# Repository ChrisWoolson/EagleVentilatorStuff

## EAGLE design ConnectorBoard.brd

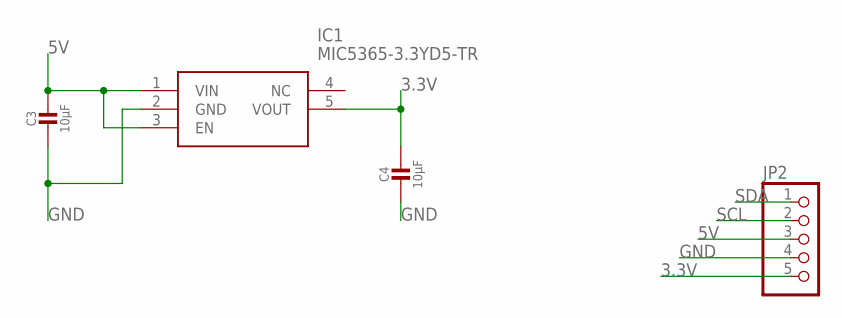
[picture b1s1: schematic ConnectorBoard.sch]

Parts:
C3, C4: 10µF; 0805-NO
IC1: MIC5365-3.3YD5-TR; SOT95P280X100-5N
JP2: PINHD-1X55X2MM; 1_05X2MM

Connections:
3.3V: C4.1, IC1.5 (VOUT), JP2.5
5V: C3.1, IC1.1 (VIN), IC1.3 (EN), JP2.3
GND: C3.2, C4.2, IC1.2 (GND), JP2.4
SCL: JP2.2
SDA: JP2.1

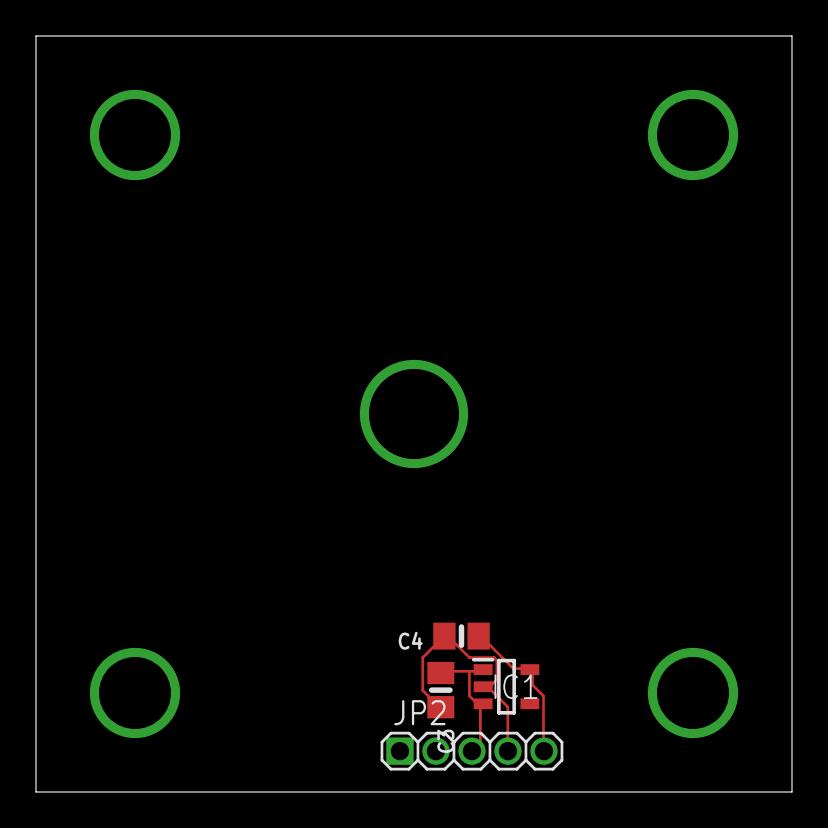
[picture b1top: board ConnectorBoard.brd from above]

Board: 2 copper layers, 42.0 x 42.0 mm, 4 parts (0 on the bottom side), 3 nets.

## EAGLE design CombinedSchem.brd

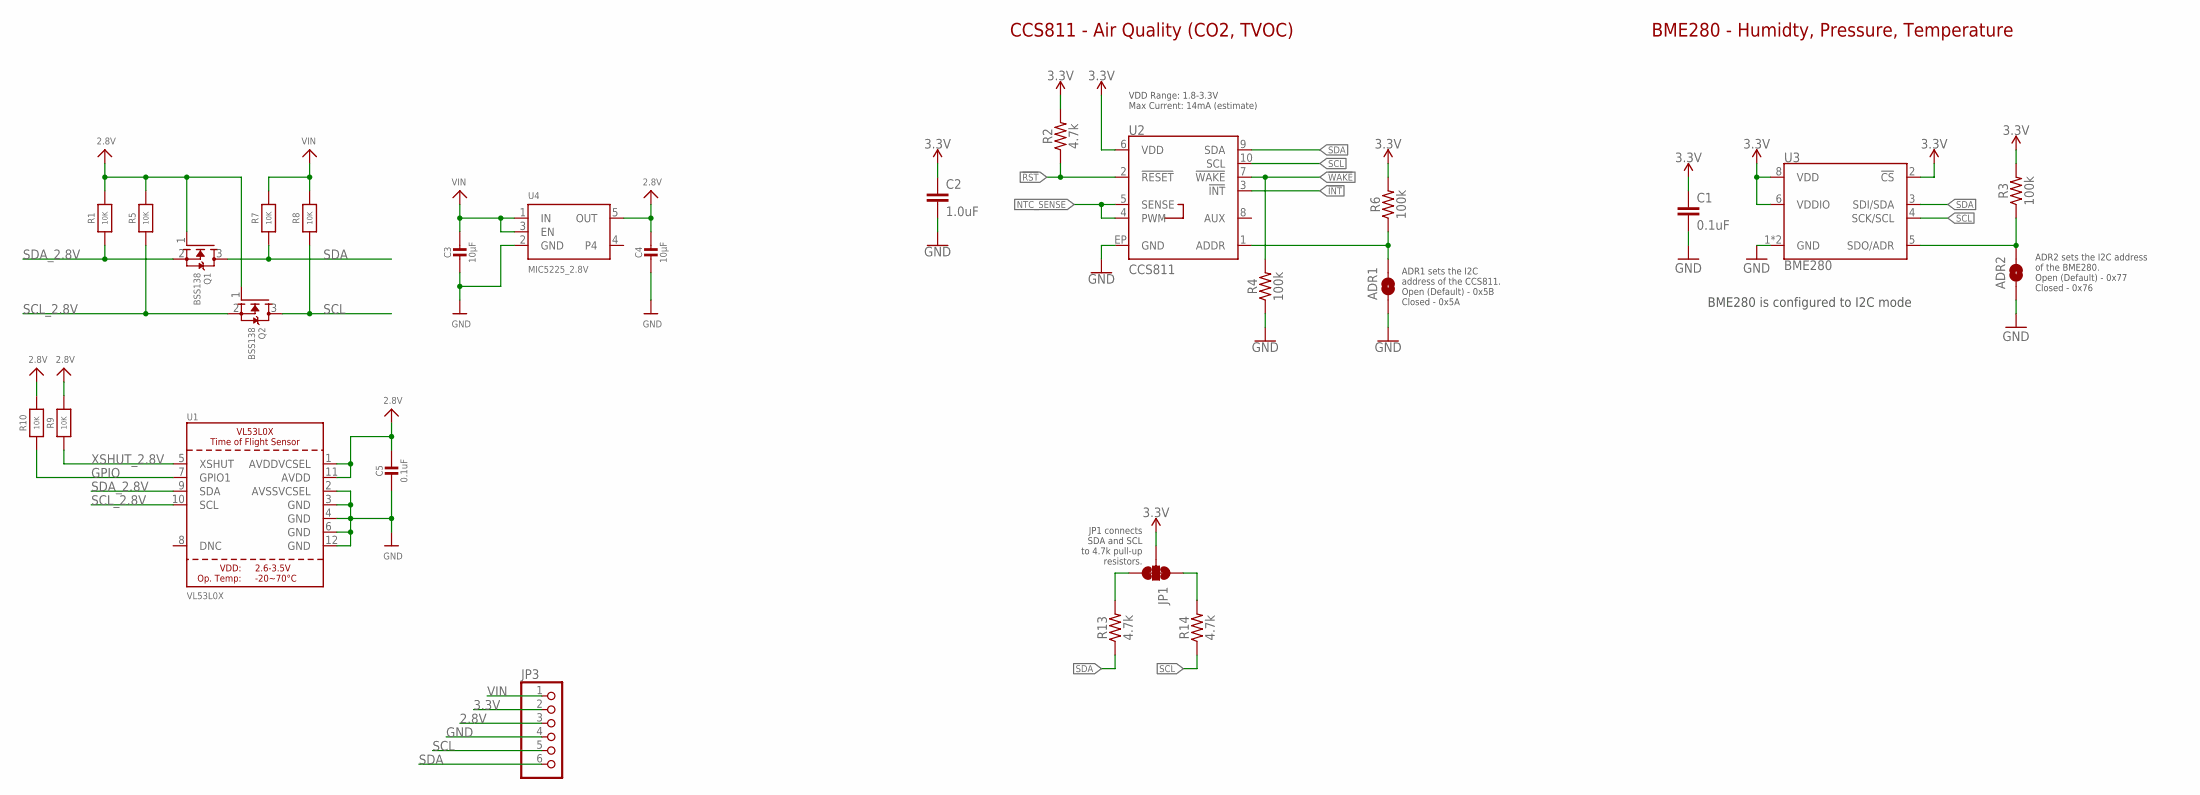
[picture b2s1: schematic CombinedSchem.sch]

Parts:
ADR1, ADR2: JUMPER-SMT_2_NO_SILK; SMT-JUMPER_2_NO_SILK
C1: 0.1uF; 0603
C2: 1.0uF; 0603
C3, C4: 10µF; 0805-NO
C5: 0.1uF; 0805-NO
JP1: JUMPER-SMT_3_2-NC_TRACE_SILK; SMT-JUMPER_3_2-NC_TRACE_SILK
JP3: PINHD-1X6CLEAN; 1X06-CLEAN
Q1, Q2: BSS138; SOT23-WIDE
R1, R5, R7, R8, R9, R10: 10K; 0805-NO
R2, R13, R14: 4.7k; 0603
R3, R4, R6: 100k; 0603
U1: VL53L0X; LGA12_ST
U2: CCS811; LGA10
U3: BME280; LGA-8-2.5X2.5
U4: MIC5225_2.8V; SOT23-5

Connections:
2.8V: C4.1, C5.1, JP3.3, Q1.1 (G), Q2.1 (G), R1.2, R5.2, R9.2, R10.2, U1.1 (AVDDVCSEL), U1.11 (AVDD), U4.5 (OUT)
3.3V: C1.1, C2.1, JP1.2, JP3.2, R2.2, R3.2, R6.2, U2.6 (VDD), U3.2 (!CS), U3.6 (VDDIO), U3.8 (VDD)
!INT: U2.3 (!INT!)
!RST: R2.1, U2.2 (!RESET!)
!WAKE: R4.2, U2.7 (!WAKE!)
CCS811_ADDR: ADR1.2, R6.1, U2.1 (ADDR)
GND: ADR1.1, ADR2.1, C1.2, C2.2, C3.2, C4.2, C5.2, JP3.4, R4.1, U1.2 (AVSSVCSEL), U1.3 (GND), U1.4 (GND), U1.6 (GND), U1.12 (GND), U2.EP (GND), U3.1 (GND), U3.7 (GND), U4.2 (GND)
GPIO: R10.1, U1.7 (GPIO1)
unnamed: JP1.3, R13.2
unnamed: JP1.1, R14.2
NTC_SENSE: U2.4 (PWM), U2.5 (SENSE)
SCL: JP3.5, Q2.3 (D), R8.1, R14.1, U2.10 (SCL), U3.4 (SCK/SCL)
SCL_2.8V: Q2.2 (S), R5.1, U1.10 (SCL)
SDA: JP3.6, Q1.3 (D), R7.1, R13.1, U2.9 (SDA), U3.3 (SDI/SDA)
SDA_2.8V: Q1.2 (S), R1.1, U1.9 (SDA)
SDO/ADR: ADR2.2, R3.1, U3.5 (SDO/ADR)
VIN: C3.1, JP3.1, R7.2, R8.2, U4.1 (IN), U4.3 (EN)
XSHUT_2.8V: R9.1, U1.5 (XSHUT)

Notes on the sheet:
VDD Range: 1.8-3.3V Max Current: 14mA (estimate)
CCS811 - Air Quality (CO2, TVOC)
ADR1 sets the I2C address of the CCS811. Open (Default) - 0x5B Closed - 0x5A
JP1 connects SDA and SCL to 4.7k pull-up resistors.
ADR2 sets the I2C address of the BME280. Open (Default) - 0x77 Closed - 0x76
BME280 is configured to I2C mode
BME280 - Humidty, Pressure, Temperature

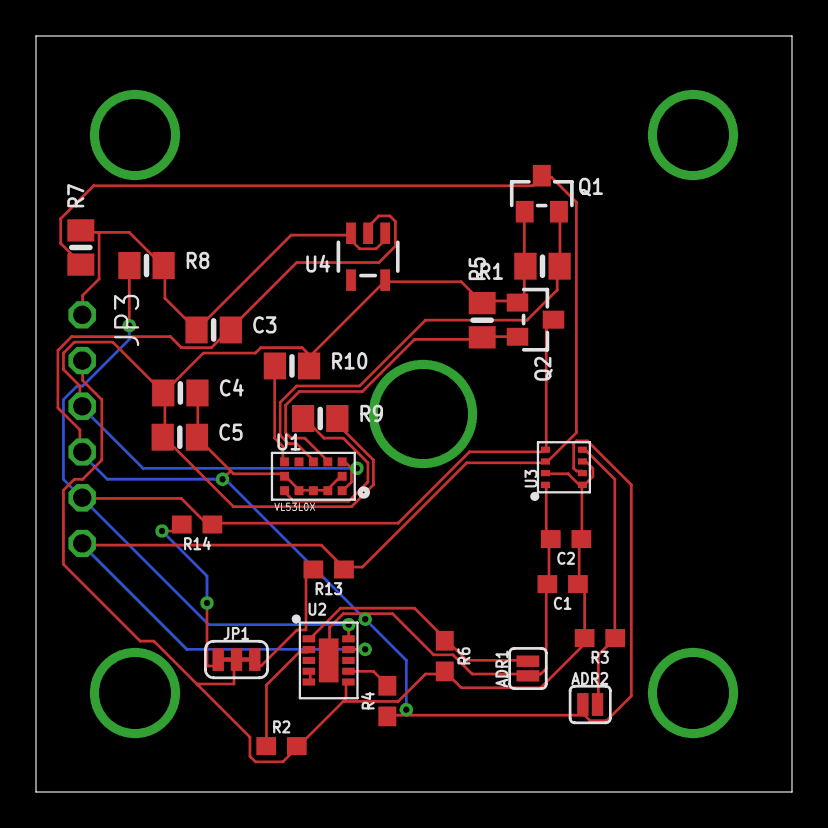
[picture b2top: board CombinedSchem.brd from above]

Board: 2 copper layers, 42.0 x 42.0 mm, 27 parts (0 on the bottom side), 17 nets.

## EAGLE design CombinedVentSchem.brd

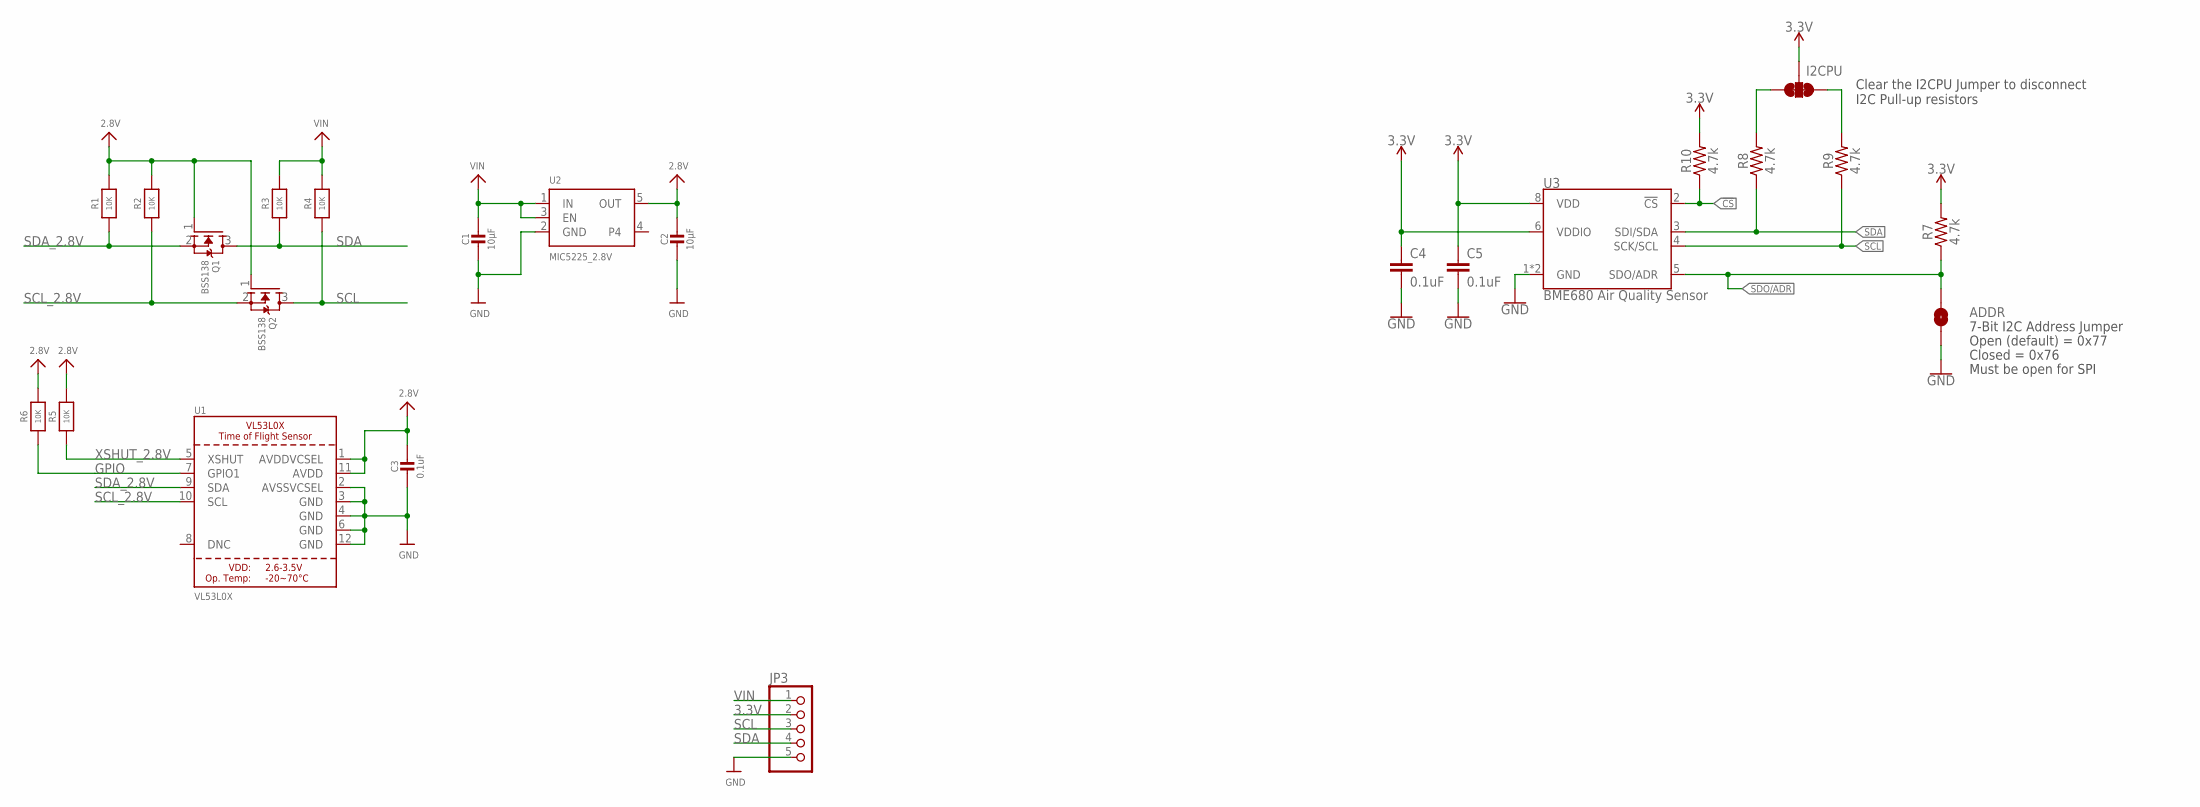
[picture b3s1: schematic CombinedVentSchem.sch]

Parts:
ADDR: JUMPER-SMT_2_NO_SILK; SMT-JUMPER_2_NO_SILK
C1, C2: 10µF; 0805-NO
C3: 0.1uF; 0805-NO
C4, C5: 0.1uF; 0603
I2CPU: I2C PU; SMT-JUMPER_3_2-NC_TRACE_SILK
JP3: PINHD-1X55X2MM; 1_05X2MM
Q1, Q2: BSS138; SOT23-WIDE
R1, R2, R3, R4, R5, R6: 10K; 0805-NO
R7, R8, R9, R10: 4.7k; 0603@1
U1: VL53L0X; LGA12_ST
U2: MIC5225_2.8V; SOT23-5
U3: BME680 Air Quality Sensor; LGA3.0X3.0

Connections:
2.8V: C2.1, C3.1, Q1.1 (G), Q2.1 (G), R1.2, R2.2, R5.2, R6.2, U1.1 (AVDDVCSEL), U1.11 (AVDD), U2.5 (OUT)
3.3V: C4.1, C5.1, I2CPU.2, JP3.2, R7.2, R10.2, U3.6 (VDDIO), U3.8 (VDD)
!CS: R10.1, U3.2 (!CS)
GND: ADDR.1, C1.2, C2.2, C3.2, C4.2, C5.2, JP3.5, U1.2 (AVSSVCSEL), U1.3 (GND), U1.4 (GND), U1.6 (GND), U1.12 (GND), U2.2 (GND), U3.1 (GND), U3.7 (GND)
GPIO: R6.1, U1.7 (GPIO1)
unnamed: I2CPU.3, R8.2
unnamed: I2CPU.1, R9.2
SCL: JP3.3, Q2.3 (D), R4.1, R9.1, U3.4 (SCK/SCL)
SCL_2.8V: Q2.2 (S), R2.1, U1.10 (SCL)
SDA: JP3.4, Q1.3 (D), R3.1, R8.1, U3.3 (SDI/SDA)
SDA_2.8V: Q1.2 (S), R1.1, U1.9 (SDA)
SDO/ADR: ADDR.2, R7.1, U3.5 (SDO/ADR)
VIN: C1.1, JP3.1, R3.2, R4.2, U2.1 (IN), U2.3 (EN)
XSHUT_2.8V: R5.1, U1.5 (XSHUT)

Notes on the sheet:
7-Bit I2C Address Jumper
Open (default) = 0x77
Closed = 0x76
Must be open for SPI
Clear the I2CPU Jumper to disconnect I2C Pull-up resistors

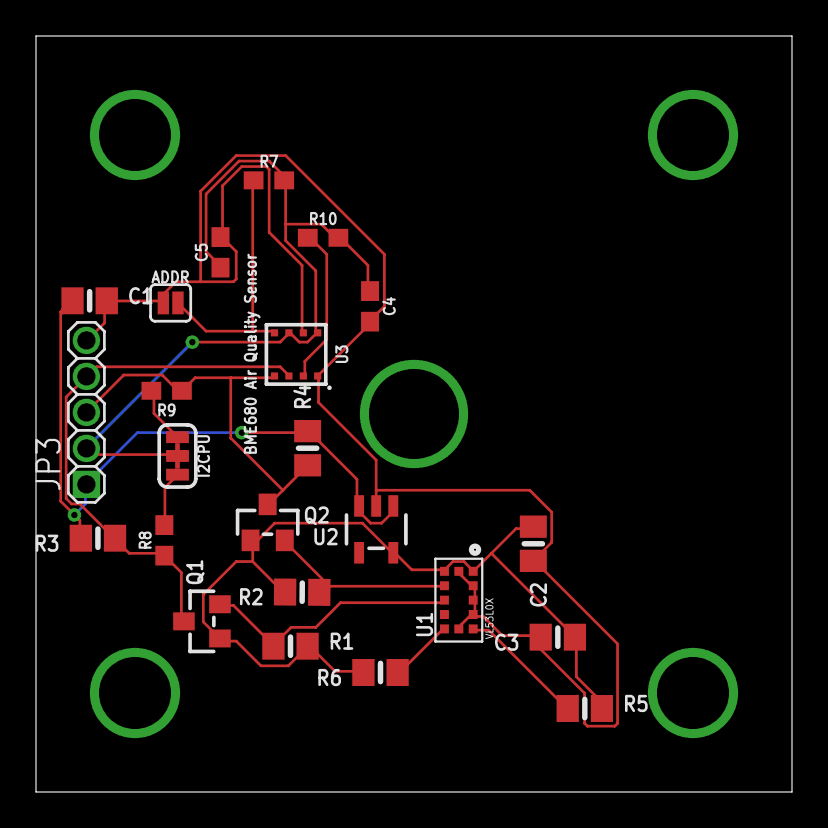
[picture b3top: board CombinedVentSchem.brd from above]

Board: 2 copper layers, 42.0 x 42.0 mm, 23 parts (0 on the bottom side), 14 nets.

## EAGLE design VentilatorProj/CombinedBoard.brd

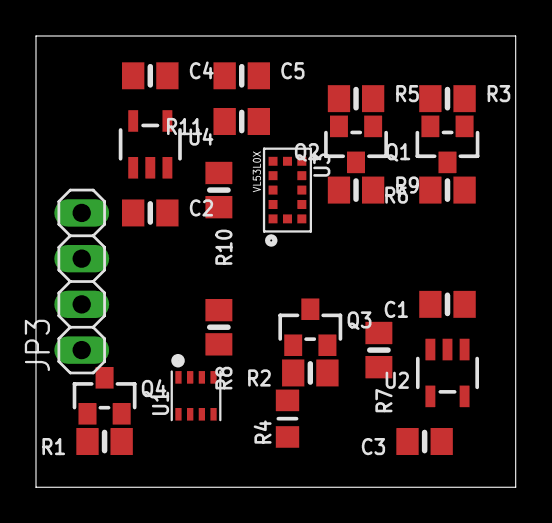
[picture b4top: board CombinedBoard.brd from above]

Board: 2 copper layers, 26.6 x 25.1 mm, 26 parts (1 on the bottom side), 14 nets, no tracks yet.

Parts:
C1, C3: 10uF; 0805-NO
C2, C4: 10µF; 0805-NO
C5: 0.1uF; 0805-NO
D2: 1N4148; SOD-323
JP3: 1X04
Q1, Q2, Q3, Q4: BSS138; SOT23-WIDE
R1, R2, R3, R5, R6, R7, R8, R9, R10, R11: 10K; 0805-NO
R4: 10K; _0805MP
U1: BME280
U2: MIC5225-3.3; SOT23-5
U3: VL53L0X; LGA12_ST
U4: MIC5225_2.8V; SOT23-5

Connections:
2.8V: C4.1, C5.1, Q1.1, Q2.1, R3.2, R5.2, R10.2, R11.2, U3.1, U3.11, U4.5
3.3V: C3.1, Q3.1, Q4.1, R1.2, R2.2, R4.2, U1.6, U1.8, U2.5
5.0V: C1.1, C2.1, JP3.1, R6.2, R7.2, R8.2, R9.2, U2.1, U2.3, U4.1, U4.3
CS_3V: D2.A, U1.2
GND: C1.2, C2.2, C3.2, C4.2, C5.2, JP3.2, U1.1, U1.7, U2.2, U3.2, U3.3, U3.4, U3.6, U3.12, U4.2
GPIO: R11.1, U3.7
SCK_3V: Q3.2, R2.1, U1.4
SCL: JP3.4, Q2.3, Q3.3, R7.1, R9.1
SCL_2.8V: Q2.2, R5.1, U3.10
SDA: JP3.3, Q1.3, Q4.3, R6.1, R8.1
SDA_2.8V: Q1.2, R3.1, U3.9
SDI_3V: Q4.2, R1.1, U1.3
SDO/ADR_3V: R4.1, U1.5
XSHUT_2.8V: R10.1, U3.5

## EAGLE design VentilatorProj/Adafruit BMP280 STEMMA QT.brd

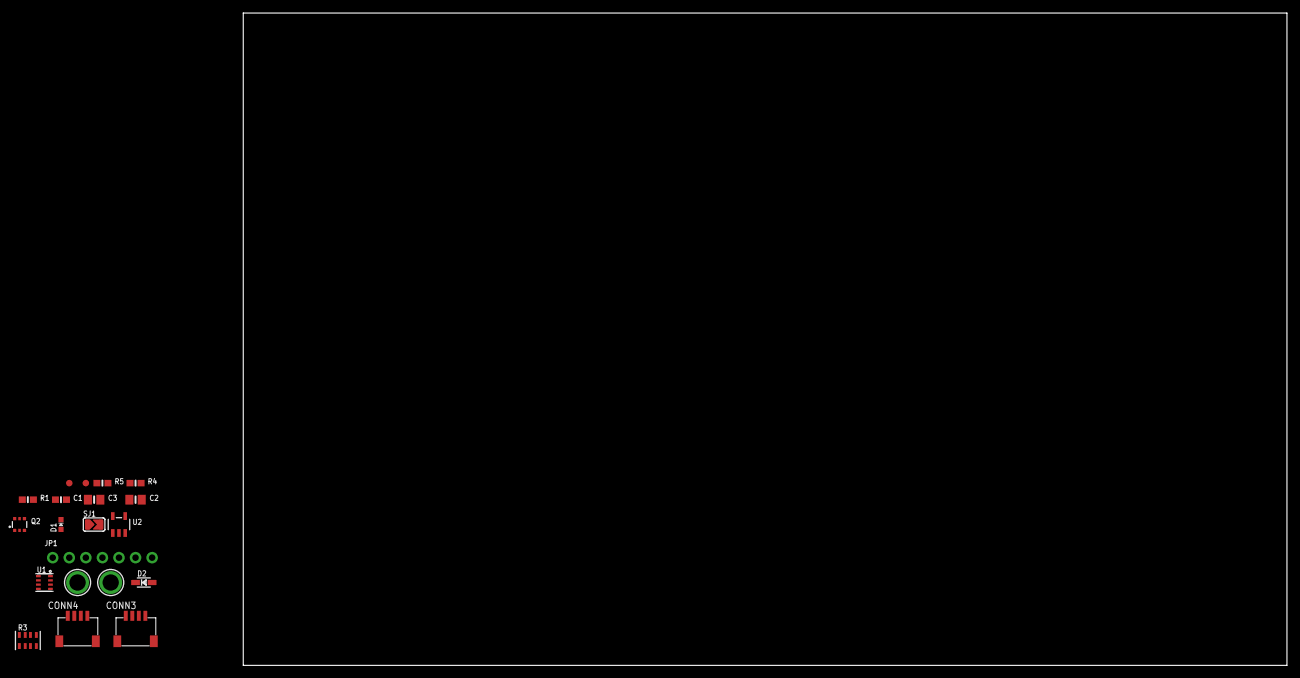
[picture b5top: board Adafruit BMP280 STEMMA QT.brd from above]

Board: 2 copper layers, 160.0 x 100.0 mm, 20 parts (0 on the bottom side), 11 nets, no tracks yet.

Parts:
C1: 0.1uF; 0603-NO
C2, C3: 10uF; 0805-NO
CONN3, CONN4: STEMMA_I2C_QT; JST_SH4
D1: GREEN; CHIPLED_0603_NOOUTLINE
D2: 1N4148; SOD-323
FID3, FID4: FIDUCIAL_1MM
JP1: 1X07_ROUND_70
Q2: BSS138; SOT363
R1, R4, R5: 10K; 0603-NO
R3: 10K; RESPACK_4X0603
SJ1: SOLDERJUMPER_ARROW_NOPASTE
U1: BMX280_COMBO
U2: AP2112K-3.3; SOT23-5
U$1, U$17: MOUNTINGHOLE2.5; MOUNTINGHOLE_2.5_PLATED

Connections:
3.3V: C1.1, C3.1, JP1.2, Q2.2, Q2.5, R1.1, R3.2, R3.4, R4.2, R5.2, U1.6, U1.8, U2.5
CS: D2.C, JP1.7
CS_3V: D2.A, R5.1, U1.2
GND: C1.2, C2.2, C3.2, CONN3.1, CONN4.1, D1.C, JP1.3, SJ1.2, U1.1, U1.7, U2.2
unnamed: D1.A, R1.2
SCK/SCL: CONN3.4, CONN4.4, JP1.4, Q2.6, R3.8
SCK_3V: Q2.1, R3.7, U1.4
SDI/SDA: CONN3.3, CONN4.3, JP1.6, Q2.3, R3.6
SDI_3V: Q2.4, R3.5, U1.3
SDO/ADR: JP1.5, R4.1, SJ1.1, U1.5
VCC: C2.1, CONN3.2, CONN4.2, JP1.1, R3.1, R3.3, U2.1, U2.3

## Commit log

2021-06-20 The actual combined file
2021-08-14 New Upload
2021-08-14 Deleted stuff

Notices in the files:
parts and their libraries:
SparkFun-Jumpers: Licensing: Creative Commons ShareAlike 4.0 International - https://creativecommons.org/licenses/by-sa/4.0
microbuilder: This work is placed in the public domain, and may be freely used for commercial and non-commercial work with the following conditions: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
